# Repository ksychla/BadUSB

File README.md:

# BadUSB

## Building

1. Install compiler 
	Download compiler from [arm developer](https://developer.arm.com/downloads/-/gnu-rm)
	```bash
	tar -xvjf gcc-arm-none-eabi-10.3-2021.10-x86_64-linux.tar.bz2
	sudo mv gcc-arm-none-eabi-10.3-2021.10 /opt
	export PATH=/opt/gcc-arm-none-eabi-10.3-2021.10/bin:$PATH
	```
2. Install st-link
	```bash
	sudo pacman -S stlink
	```
3. Build and flash the firmware
	```bash
	git clone https://github.com/ksychla/BadUSB.git
	cd BadUSB/
	make
	```

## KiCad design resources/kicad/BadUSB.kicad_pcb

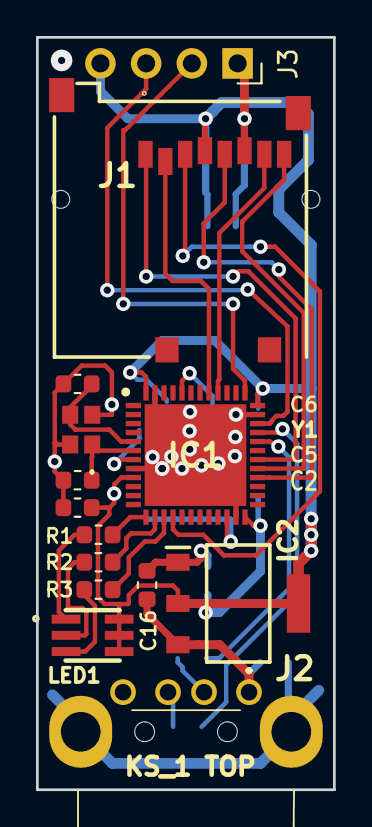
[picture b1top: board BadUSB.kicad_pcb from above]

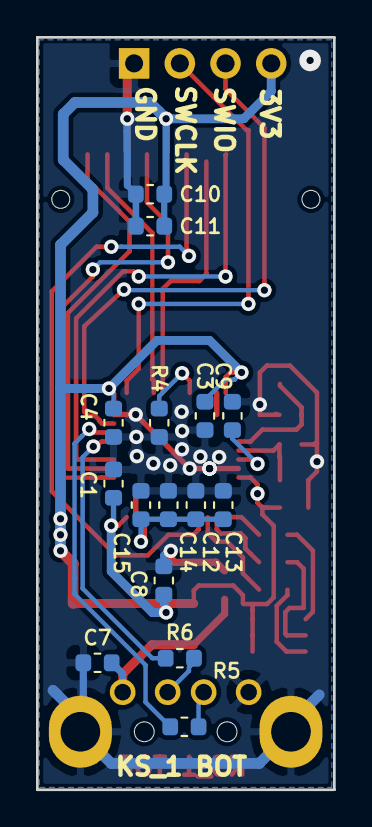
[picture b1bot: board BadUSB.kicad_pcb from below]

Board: 2 copper layers, 16.5 x 41.8 mm, 31 parts (15 on the bottom side), 26 nets.

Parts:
C1, C2, C3, C4, C9, C11: 100n; C_0603_1608Metric
C5, C6: 12p; C_0603_1608Metric
C7, C8, C10, C12, C13, C14, C15, C16: 1u; C_0603_1608Metric
H1, H2: MountingHole; MountingHole_2.2mm_M2
IC1: STM32F411CEU6; QFN50P700X700X60-49N-D
IC2: ASM1117CD-3.3; SOT229P700X180-4N
J1: 47352-1001
J2: USB-AM-S-F-B-TH; USBAMSFBTH
J3: Conn_01x04; PinSocket_1x04_P2.54mm_Horizontal
LED1: ASMT-YTB2-0BB02; ASMT-YTC7-0AA02
R1: 470R; R_0603_1608Metric
R2, R3, R5, R6: R; R_0603_1608Metric
R4: 10k; R_0603_1608Metric
Y1: LFXTAL069392Cutt

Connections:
+3V3: C1.1, C2.1, C3.1, C4.1, C8.1, C10.1, C11.1, IC1.9, IC1.24, IC1.36, IC1.48, IC2.2, IC2.4, J1.4, J3.4, LED1.4, LED1.5, LED1.6
+5V: C7.1, C16.2, IC2.3, J2.1
/CLK: IC1.28, J1.5
/CMD: IC1.16, J1.3
/D0: IC1.40, J1.7
/D1: IC1.29, J1.8
/D2: IC1.30, J1.1
/D3: IC1.41, J1.2
/D+: IC1.33, R5.1
/D-: IC1.32, R6.1
/DEB-CLK: IC1.37, J3.2
/DEB-IO: IC1.34, J3.3
/LD_B: IC1.15, R3.1
/LD_G: IC1.14, R2.1
/LD_R: IC1.13, R1.1
GND: C1.2, C2.2, C3.2, C4.2, C5.2, C6.2, C7.2, C8.2, C9.2, C10.2, C11.2, C12.2, C13.2, C14.2, C15.2, C16.1, IC1.8, IC1.23, IC1.35, IC1.47, IC1.49, IC2.1, J1.6, J2.4, J2.MH1, J2.MH2, J3.1, R4.1, Y1.2, Y1.4
unnamed: C5.1, IC1.6, Y1.1
unnamed: C6.1, IC1.5, Y1.3
unnamed: C9.1, IC1.7
unnamed: C12.1, C13.1, C14.1, C15.1, IC1.22
unnamed: IC1.44, R4.2
unnamed: J2.2, R6.2
unnamed: J2.3, R5.2
unnamed: LED1.1, R1.2
unnamed: LED1.2, R2.2
unnamed: LED1.3, R3.2

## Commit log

2022-05-13 Configure cmake project
2022-05-13 Code refactor
2022-05-14 Add kicad project
2022-05-31 Working keyboard interface
2022-05-31 Working keyboard interface v2
2022-06-01 Add encoding strings
2022-06-06 Add not working SDIO
2022-06-06 Working SDIO
2022-06-10 Changes for final product
2022-06-12 Change clock config for final board
2022-06-14 Working Keyboard
2022-06-16 Refactor hid usb
2022-06-16 Add usb msc files
2022-06-16 Working usb msc with hid
2022-06-22 Add optimization and tests
2022-06-22 Add windows support
2022-06-27 Add large files compatibility
2022-06-29 Add more delay
2022-08-10 Add more stats tests
2022-08-10 Add readme
2022-08-10 Fix readme
2022-08-10 Fix readme v2
2022-08-10 Fix readme v3
2022-08-30 Change LED functionality and Add final tests
